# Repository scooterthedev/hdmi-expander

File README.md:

# USB-PD Charger

This board is capabe of taking in USB A input, and sending a variable amount of power to a usb-c device like a phone that supports usb pd charging.

## Photos

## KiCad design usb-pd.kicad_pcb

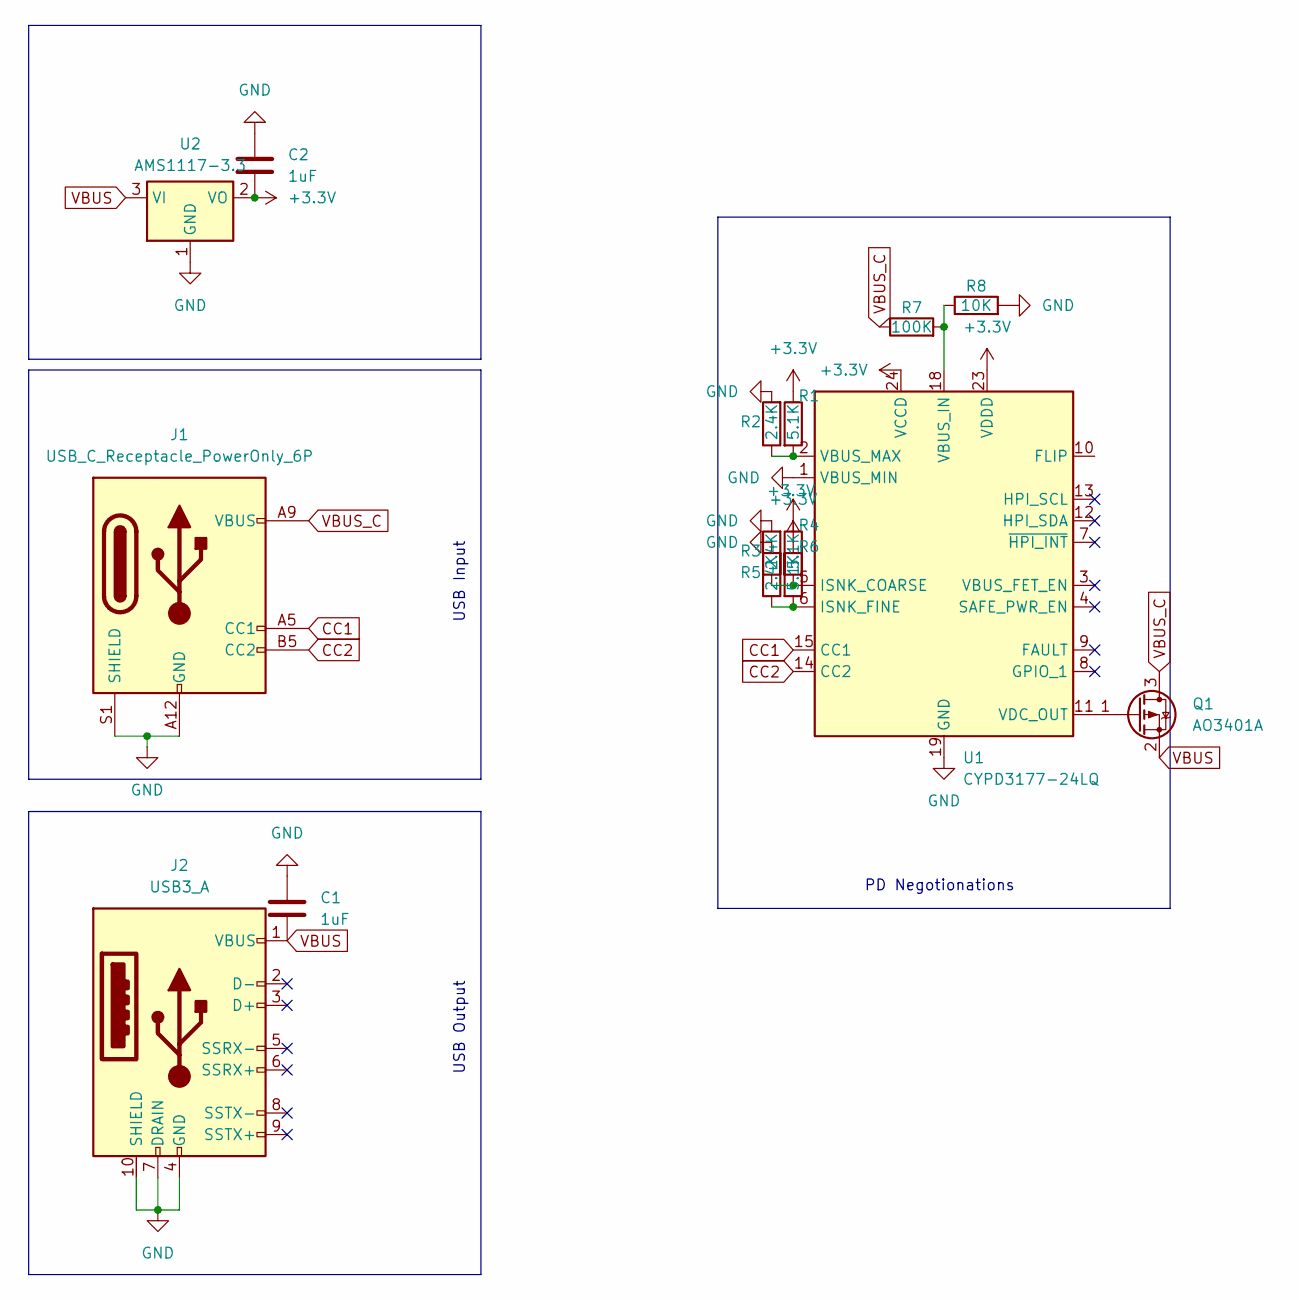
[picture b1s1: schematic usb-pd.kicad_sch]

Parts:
C1, C2: 1uF; C_0603_1608Metric
J1: USB_C_Receptacle_PowerOnly_6P; USB_C_Receptacle_HCTL_HC-TYPE-C-16P-01A
J2: USB3_A; USB3_A_Molex_48406-0001_Horizontal_Stacked
Q1: AO3401A; SOT-23
R1, R4, R6: 5.1K; R_0603_1608Metric
R2, R3, R5: 2.4K; R_0603_1608Metric
R7: 100K; R_0603_1608Metric
R8: 10K; R_0603_1608Metric
U1: CYPD3177-24LQ; QFN-24-1EP_4x4mm_P0.5mm_EP2.75x2.75mm
U2: AMS1117-3.3; SOT-223-3_TabPin2

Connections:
+3.3V: C2.2, R1.1, R4.1, R6.1, U1.23 (VDDD), U1.24 (VCCD), U2.2 (VO)
CC1: J1.A5 (CC1), U1.15 (CC1)
CC2: J1.B5 (CC2), U1.14 (CC2)
GND: C1.1, C2.1, J1.A12 (GND), J1.B12 (GND), J1.S1 (SHIELD), J2.4 (GND), J2.7 (DRAIN), J2.10 (SHIELD), R2.2, R3.2, R5.2, R8.2, U1.1 (VBUS_MIN), U1.19 (GND), U1.22 (GND), U1.25 (GND), U2.1 (GND)
unnamed: Q1.1 (G), U1.11 (VDC_OUT)
unnamed: R3.1, R4.2, U1.5 (ISNK_COARSE)
unnamed: R5.1, R6.2, U1.6 (ISNK_FINE)
unnamed: R7.2, R8.1, U1.18 (VBUS_IN)
unnamed: R1.2, R2.1, U1.2 (VBUS_MAX)
VBUS: C1.2, J2.1 (VBUS), Q1.2 (S), U2.3 (VI)
VBUS_C: J1.A9 (VBUS), J1.B9 (VBUS), Q1.3 (D), R7.1

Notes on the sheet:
USB Output
PD Negotionations
USB Input

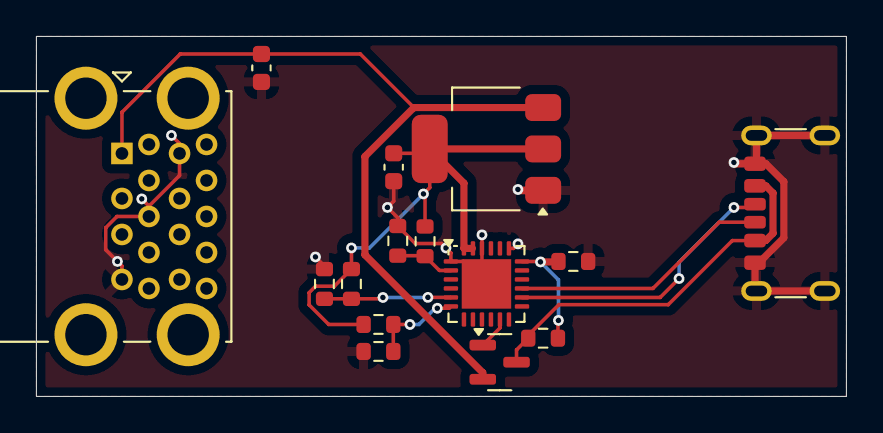
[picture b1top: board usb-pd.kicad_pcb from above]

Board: 2 copper layers, 45.0 x 20.0 mm, 15 parts (0 on the bottom side), 11 nets.

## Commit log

2025-07-21 Changed to usb-pd
2025-07-21 workin on the schematic
2025-07-21 trying to work on the PD IC some more
2025-07-21 I think I finished the schematic
2025-07-21 uuh, routing is done lol
2025-07-21 adding silkscreen and stuff
